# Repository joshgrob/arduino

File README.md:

# arduino
Various arduino projects

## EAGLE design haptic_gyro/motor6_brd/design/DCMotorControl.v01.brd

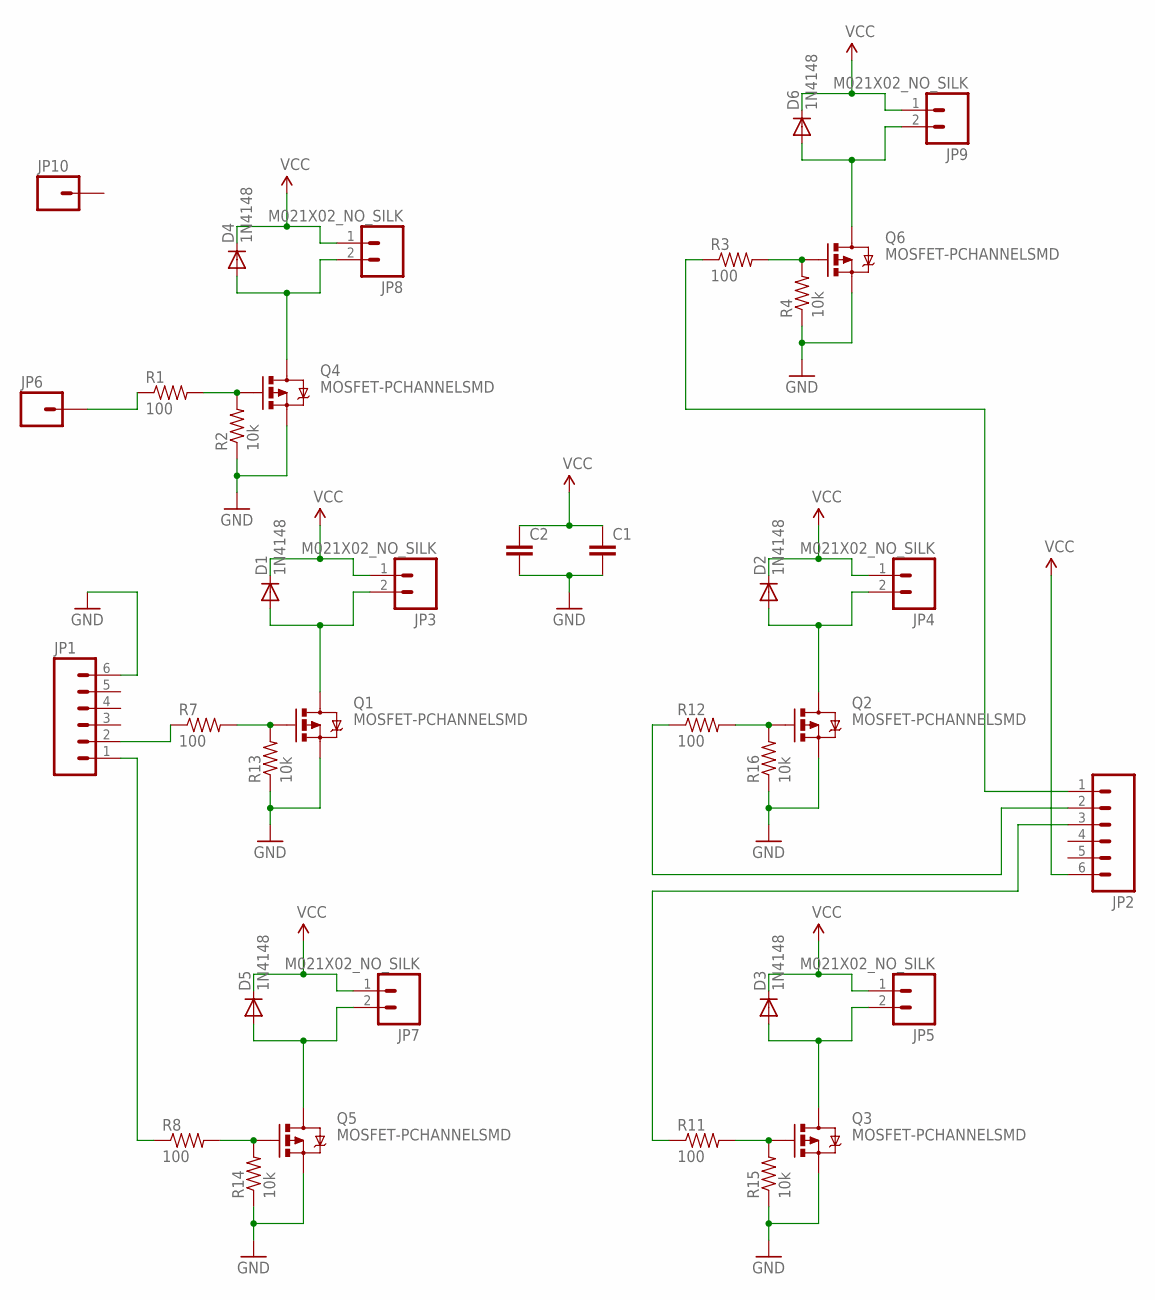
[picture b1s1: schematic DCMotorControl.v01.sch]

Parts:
C1, C2: CAP0805; 0805
D1, D2, D3, D4, D5, D6: 1N4148; SOD323-R
JP1, JP2: M06NO_SILK; 1X06_NO_SILK
JP3, JP4, JP5, JP7, JP8, JP9: M021X02_NO_SILK; 1X02_NO_SILK
JP6, JP10: M01NOSILK-KIT; 1X01NS-KIT
Q1, Q2, Q3, Q4, Q5, Q6: MOSFET-PCHANNELSMD; SOT23-3
R1, R3, R7, R8, R11, R12: 100; 0603-RES
R2, R4, R13, R14, R15, R16: 10k; 0603-RES

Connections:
GND: C1.2, C2.2, JP1.6, Q1.2 (S), Q2.2 (S), Q3.2 (S), Q4.2 (S), Q5.2 (S), Q6.2 (S), R2.1, R4.1, R13.1, R14.1, R15.1, R16.1
unnamed: D1.A, JP3.2, Q1.3 (D)
unnamed: Q1.1 (G), R7.2, R13.2
unnamed: JP1.2, R7.1
unnamed: D5.A, JP7.2, Q5.3 (D)
unnamed: Q5.1 (G), R8.2, R14.2
unnamed: JP1.1, R8.1
unnamed: D2.A, JP4.2, Q2.3 (D)
unnamed: Q2.1 (G), R12.2, R16.2
unnamed: JP2.2, R12.1
unnamed: D3.A, JP5.2, Q3.3 (D)
unnamed: Q3.1 (G), R11.2, R15.2
unnamed: JP2.3, R11.1
unnamed: D4.A, JP8.2, Q4.3 (D)
unnamed: Q4.1 (G), R1.2, R2.2
unnamed: JP6.1, R1.1
unnamed: D6.A, JP9.2, Q6.3 (D)
unnamed: Q6.1 (G), R3.2, R4.2
unnamed: JP2.1, R3.1
VCC: C1.1, C2.1, D1.C, D2.C, D3.C, D4.C, D5.C, D6.C, JP2.6, JP3.1, JP4.1, JP5.1, JP7.1, JP8.1, JP9.1

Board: 2 copper layers, 36 parts (2 on the bottom side), 20 nets, no tracks yet.

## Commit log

2015-10-06 First version of gyro, haptic controller. Not functional
2015-10-20 Refactor gyro functions
2015-10-25 Changed update rate for motors. Still buggy
2015-11-03 Isolating Gyro functionality
2016-02-21 Version 1 of brd ready
2016-03-01 Auto Warm Start

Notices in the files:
parts and their libraries:
SparkFun-DiscreteSemi: Licensing: Creative Commons ShareAlike 4.0 International - https://creativecommons.org/licenses/by-sa/4.0
